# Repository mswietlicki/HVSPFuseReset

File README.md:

HVSPFuseReset
=============

As simple as possible ATTiny85 HVSP fuse reset.

This project objective is to create very simple broard for HVSP (High Voltage Serial Programing) ATTiny85 fuse reset. This will enable my to use RESET pin as IO without losing ability to reprogram micro controler.

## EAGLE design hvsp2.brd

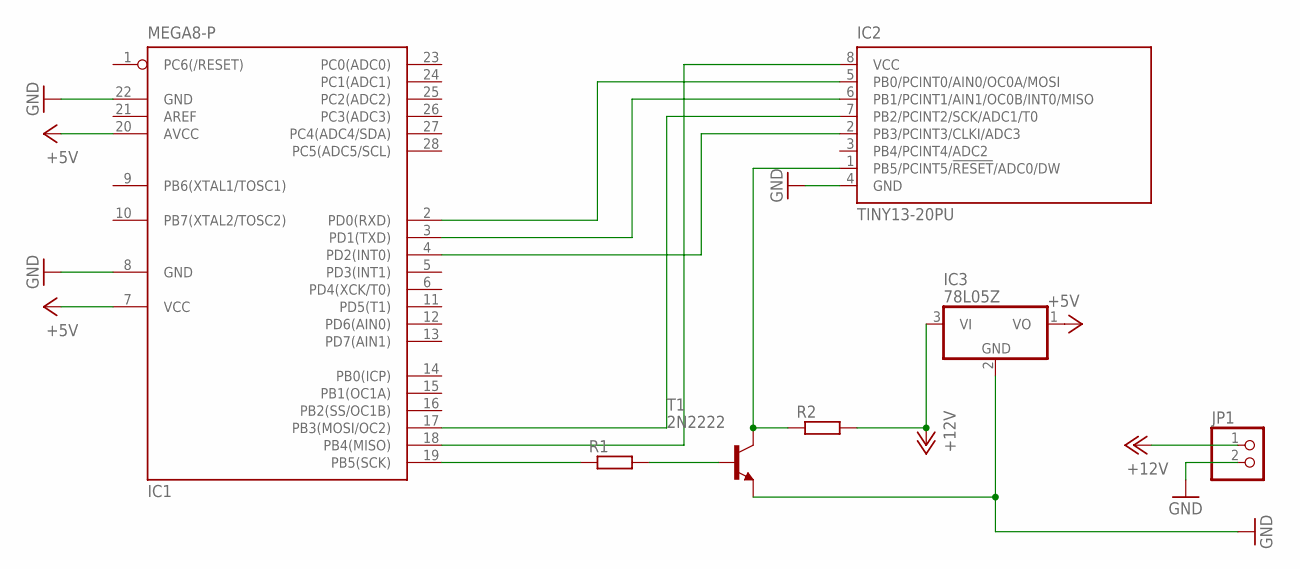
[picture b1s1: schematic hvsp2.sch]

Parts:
IC1: MEGA8-P; DIL28-3
IC2: TINY13-20PU; DIL08
IC3: 78L05Z; TO92
JP1: PINHD-1X2; 1X02
R1: R-EU_0204/7; 0204/7
R2: R-EU_0207/10; 0207/10
T1: 2N2222; TO18

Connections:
+5V: IC1.7 (VCC), IC1.20 (AVCC), IC3.1 (VO)
+12V: IC3.3 (VI), JP1.1, R2.2
GND: IC1.8 (GND), IC1.22 (GND), IC2.4 (GND), IC3.2 (GND), JP1.2, T1.1 (E)
unnamed: IC2.1 (PB5/PCINT5/!RESET!/ADC0/DW), R2.1, T1.3 (C)
unnamed: IC1.18 (PB4(MISO)), IC2.8 (VCC)
unnamed: R1.2, T1.2 (B)
unnamed: IC1.19 (PB5(SCK)), R1.1
unnamed: IC1.17 (PB3(MOSI/OC2)), IC2.7 (PB2/PCINT2/SCK/ADC1/T0)
unnamed: IC1.2 (PD0(RXD)), IC2.5 (PB0/PCINT0/AIN0/OC0A/MOSI)
unnamed: IC1.3 (PD1(TXD)), IC2.6 (PB1/PCINT1/AIN1/OC0B/INT0/MISO)
unnamed: IC1.4 (PD2(INT0)), IC2.2 (PB3/PCINT3/CLKI/ADC3)

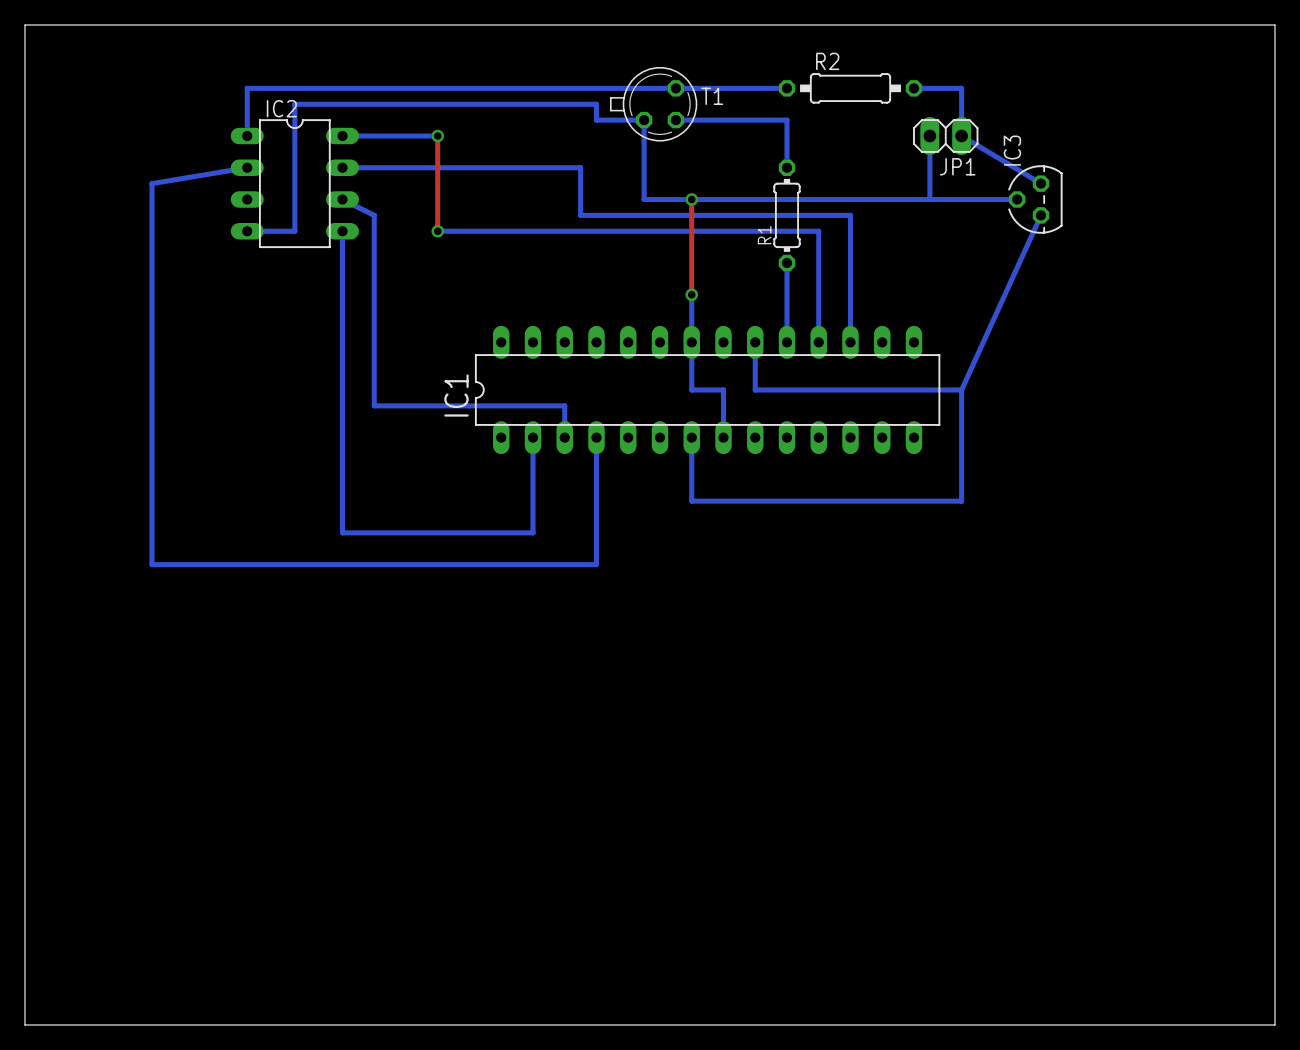
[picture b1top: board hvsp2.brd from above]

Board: 2 copper layers, 100.0 x 80.0 mm, 7 parts (0 on the bottom side), 11 nets.

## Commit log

2013-10-01 Create
2013-10-01 Added fuse.c from http://www.simpleavr.com/avr/hvsp-fuse-resetter
2013-10-01 Added original fuse.c
2013-10-01 Stripping unnecessary code and descriptions.
2013-10-01 Stripping even more and setting lfuse to 0xe2 (8Mhz).
2013-10-01 Refactoring
2013-10-08 Change pins to work with Atmega8
2013-10-08 Added board schematic
2013-10-08 Added *.*#* to ignore
2013-10-08 Added program script
2013-10-08 Fix some bugs
2013-10-09 Added Brown-out fuse
2013-10-09 Clearing code base on ScratchMonkey
